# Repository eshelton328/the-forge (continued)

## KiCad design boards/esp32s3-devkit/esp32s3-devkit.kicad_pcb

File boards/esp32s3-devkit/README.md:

# ESP32-S3 DevKit

Development board built around the [ESP32-S3-WROOM-1](https://www.espressif.com/sites/default/files/documentation/esp32-s3-wroom-1_wroom-1u_datasheet_en.pdf) module with an integrated [TPS63070](https://www.ti.com/lit/ds/symlink/tps63070.pdf) buck-boost converter and USB-C connectivity.

## Specifications

- **MCU**: ESP32-S3-WROOM-1 (Wi-Fi + BLE, dual-core, 32-bit)
- **Power**: battery only — 3×AA (≈3.0–4.8 V) on the VBAT header pin, through reverse-polarity PFET (Q1) and power switch (SW1) into a TPS63070 buck-boost (3.3 V regulated output)
- **Interface**: USB-C (USB 2.0, 16-pin receptacle) — **data only, by design**; VBUS does not power the board. Batteries must be connected and SW1 on to flash.
- **ESD protection**: USBLC6-2SC6 on USB data lines
- **Layers**: 4
- **Thickness**: 1.6mm
- **Fab targets**: JLCPCB 4-layer advanced
- **Input voltage note**: the TPS63070 accepts up to 16 V, but C3 (10 µF 0402) is 6.3 V-rated — keep VBAT ≤ ~5.5 V unless C3 is upgraded (e.g. 0805/25 V)

## Key Components

| Ref | Value | Description |
|-----|-------|-------------|
| U1 | TPS63070RNMR | Buck-boost converter (3.3V output, adjustable) |
| U2 | ESP32-S3-WROOM-1 | Wi-Fi + BLE SoC module |
| U3 | USBLC6-2SC6 | USB ESD protection |
| J1, J2 | Conn_01x17 | GPIO breakout headers (J1 pin 2 = VBAT battery input) |
| J3 | USB-C 16P | USB-C receptacle (USB 2.0, data only) |
| L1 | 1.5µH | Buck-boost inductor (XFL4020-152ME) |
| Q1 | AO3401A | Reverse-polarity protection PMOS (drain to battery) |
| SW1 | MK-12C03-G015 | SPDT slide switch — main power (latching ON/OFF) |
| SW2 | RESET | Push — ESP32 reset |
| SW3 | BOOT | Push — boot / download mode |
| D1, D3 | LED | Status indicators (D2 zener: DNP) |

## Flashing

First flash: batteries in, SW1 on, hold BOOT, tap RESET, release BOOT, then flash over native USB (CDC/DFU). Subsequent flashes work over USB without buttons.

<!-- board-images-start -->
## Board Images

_Auto-generated on merge to main._

### Schematic

### PCB Layout

| Top | Bottom |
| :---: | :---: |
|  |  |

<!-- board-images-end -->

<!-- drc-summary-start -->
## KiCad design checks

_Same layout as the KiCad check summary on pull requests (ERC, DRC, fab rules). Auto-generated on merge to main._

| Check | Result |
|:------|:-------|
| ERC | ✅ |
| DRC | 🔴 12 errors |
| Fab: jlcpcb-4layer-advanced | ✅ |

<details>
<summary><strong>DRC</strong> — 🔴 12 errors</summary>

> **Violations** (12)
>
> <details>
> <summary>🔴 <b><code>clearance</code></b> — 8 errors</summary>
>
> Clearance violation (zone clearance 0.2000 mm; actual 0.1217 mm)
> - `Track [Net-(Q1-G)] on F.Cu, length 0.4725 mm` / `Zone [/PFET] on F.Cu, priority 2`
> - `Via [Net-(Q1-G)] on F.Cu - B.Cu` / `Zone [GND] on B.Cu, priority 0`
> - `Via [Net-(Q1-G)] on F.Cu - B.Cu` / `Zone [GND] on In1.Cu, priority 0`
> - `Via [Net-(Q1-G)] on F.Cu - B.Cu` / `Zone [GND] on B.Cu, priority 0`
> - `Via [Net-(Q1-G)] on F.Cu - B.Cu` / `Zone [GND] on In1.Cu, priority 0`
> - `Track [Net-(Q1-G)] on B.Cu, length 1.1500 mm` / `Zone [GND] on B.Cu, priority 0`
> - `Track [Net-(Q1-G)] on B.Cu, length 2.5000 mm` / `Zone [GND] on B.Cu, priority 0`
> - `Pad 1 [Net-(Q1-G)] of Q1 on F.Cu` / `Zone [/PFET] on F.Cu, priority 2`
>
> </details>
>
> <details>
> <summary>🔴 <b><code>hole_clearance</code></b> — 4 errors</summary>
>
> Hole clearance violation (board setup constraints hole clearance 0.2500 mm; actual 0.0000 mm)
> - `Via [Net-(Q1-G)] on F.Cu - B.Cu` / `Zone [GND] on B.Cu, priority 0`
> - `Via [Net-(Q1-G)] on F.Cu - B.Cu` / `Zone [GND] on In1.Cu, priority 0`
> - `Via [Net-(Q1-G)] on F.Cu - B.Cu` / `Zone [GND] on B.Cu, priority 0`
> - `Via [Net-(Q1-G)] on F.Cu - B.Cu` / `Zone [GND] on In1.Cu, priority 0`
>
> </details>
>
</details>

<!-- drc-summary-end -->

## Status

**In Development** — schematic and initial PCB layout complete. Not yet fabricated.

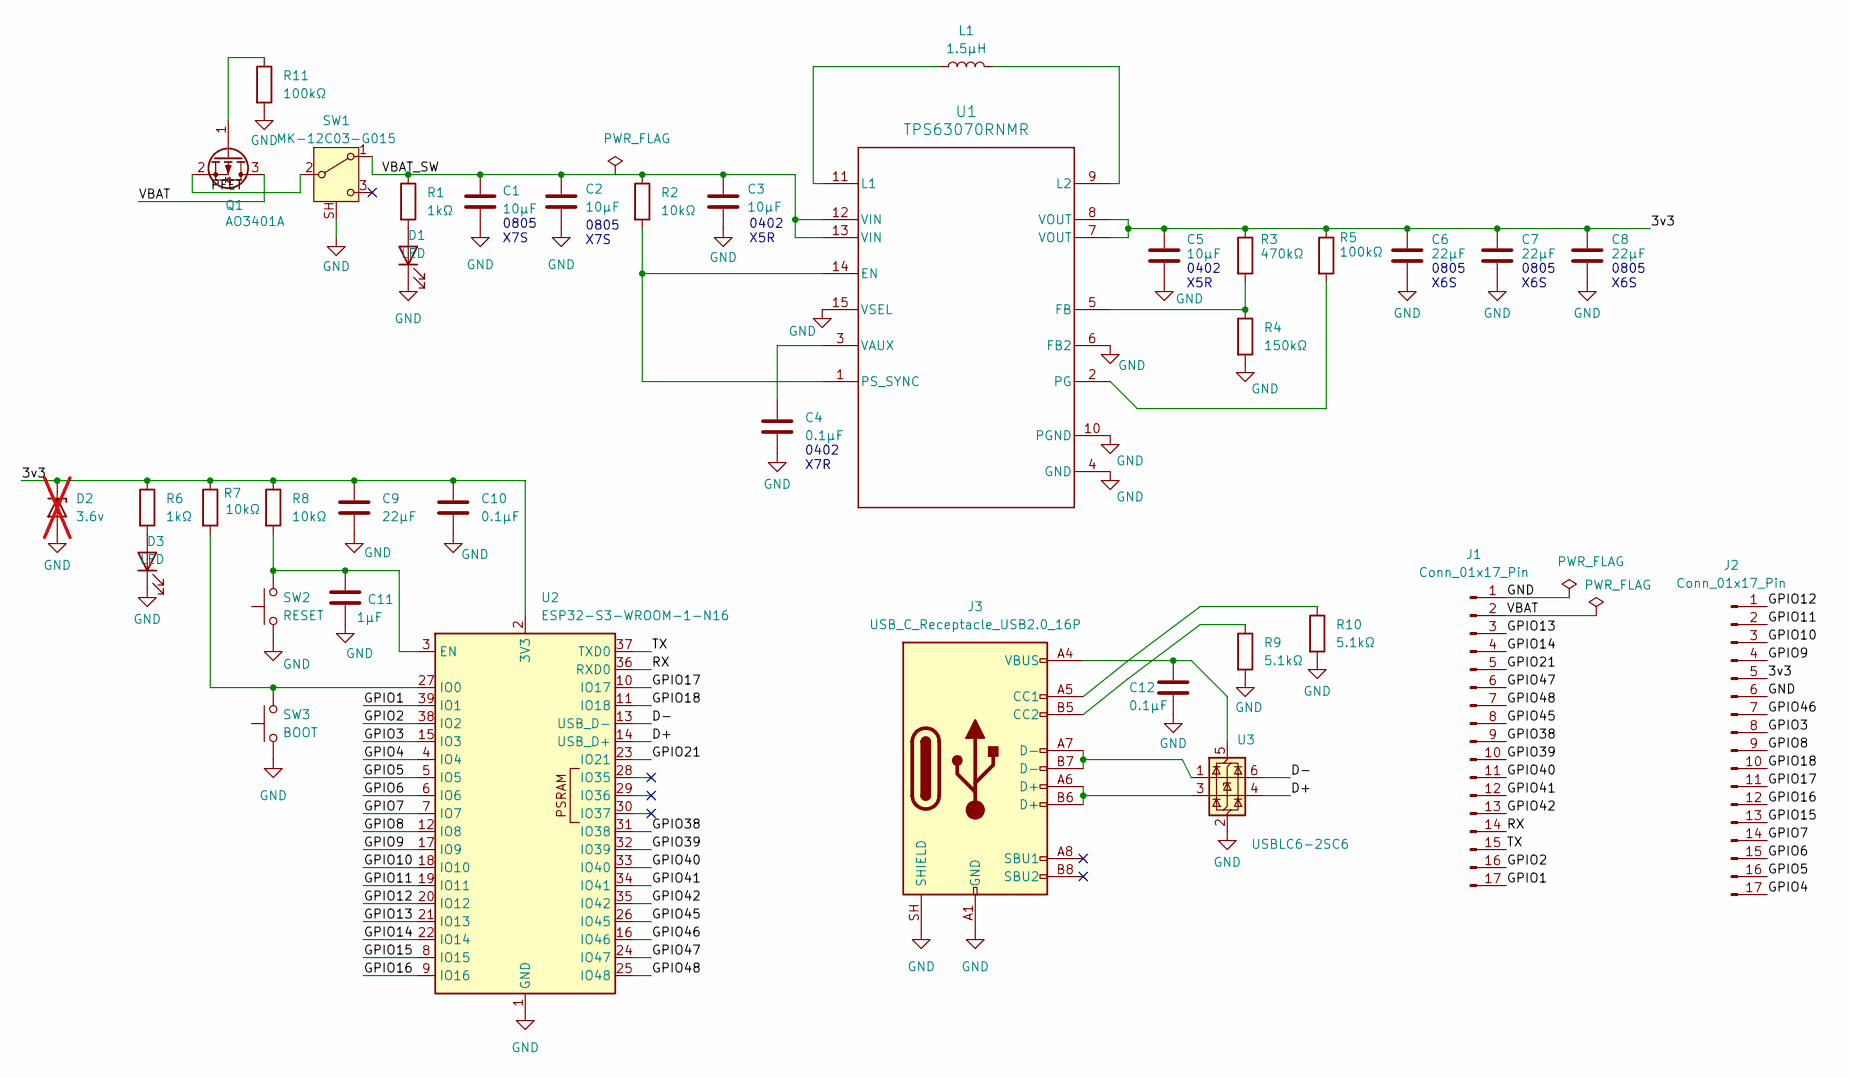
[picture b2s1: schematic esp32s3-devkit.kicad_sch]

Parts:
C1, C2: 10µF; C_0805_2012Metric
C3, C5: 10µF; C_0402_1005Metric
C4, C10, C12: 0.1µF; C_0402_1005Metric
C6, C7, C8, C9: 22µF; C_0805_2012Metric
C11: 1µF; C_0402_1005Metric
D1, D3: LED; LED_0603_1608Metric
D2: 3.6v; D_SOD-323; not fitted
J1, J2: Conn_01x17_Pin; PinHeader_1x17_P2.54mm_Vertical
J3: USB_C_Receptacle_USB2.0_16P; USB_C_Receptacle_HRO_TYPE-C-31-M-12
L1: 1.5µH; IND_XFL4020-152MEC
Q1: AO3401A; SOT-23
R1, R6: 1kΩ; R_0402_1005Metric
R2, R7, R8: 10kΩ; R_0402_1005Metric
R3: 470kΩ; R_0402_1005Metric
R4: 150kΩ; R_0402_1005Metric
R5, R11: 100kΩ; R_0402_1005Metric
R9, R10: 5.1kΩ; R_0402_1005Metric
SW1: MK-12C03-G015; SW_SPDT_Shouhan_MSK12C02
SW2: RESET; SW_Push_1P1T_XKB_TS-1187A
SW3: BOOT; SW_Push_1P1T_XKB_TS-1187A
U1: TPS63070RNMR; TPS63070
U2: ESP32-S3-WROOM-1-N16; ESP32-S3-WROOM-1
U3: USBLC6-2SC6; SOT-23-6

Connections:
/3v3: C5.1, C6.1, C7.1, C8.1, C9.1, C10.1, D2.1 (K), J2.5, R3.1, R5.1, R6.1, R7.1, R8.1, U1.7 (VOUT), U1.8 (VOUT), U2.2 (3V3)
/D+: U2.14 (USB_D+), U3.4 (I/O2)
/D-: U2.13 (USB_D-), U3.6 (I/O1)
/GPIO1: J1.17, U2.39 (IO1)
/GPIO2: J1.16, U2.38 (IO2)
/GPIO3: J2.8, U2.15 (IO3)
/GPIO4: J2.17, U2.4 (IO4)
/GPIO5: J2.16, U2.5 (IO5)
/GPIO6: J2.15, U2.6 (IO6)
/GPIO7: J2.14, U2.7 (IO7)
/GPIO8: J2.9, U2.12 (IO8)
/GPIO9: J2.4, U2.17 (IO9)
/GPIO10: J2.3, U2.18 (IO10)
/GPIO11: J2.2, U2.19 (IO11)
/GPIO12: J2.1, U2.20 (IO12)
/GPIO13: J1.3, U2.21 (IO13)
/GPIO14: J1.4, U2.22 (IO14)
/GPIO15: J2.13, U2.8 (IO15)
/GPIO16: J2.12, U2.9 (IO16)
/GPIO17: J2.11, U2.10 (IO17)
/GPIO18: J2.10, U2.11 (IO18)
/GPIO21: J1.5, U2.23 (IO21)
/GPIO38: J1.9, U2.31 (IO38)
/GPIO39: J1.10, U2.32 (IO39)
/GPIO40: J1.11, U2.33 (IO40)
/GPIO41: J1.12, U2.34 (IO41)
/GPIO42: J1.13, U2.35 (IO42)
/GPIO45: J1.8, U2.26 (IO45)
/GPIO46: J2.7, U2.16 (IO46)
/GPIO47: J1.6, U2.24 (IO47)
/GPIO48: J1.7, U2.25 (IO48)
/PFET: Q1.2 (S), SW1.2 (B)
/RX: J1.14, U2.36 (RXD0)
/TX: J1.15, U2.37 (TXD0)
/VBAT: J1.2, Q1.3 (D)
/VBAT_SW: C1.1, C2.1, C3.1, R1.1, R2.1, SW1.1 (A), U1.12 (VIN), U1.13 (VIN)
GND: C1.2, C2.2, C3.2, C4.2, C5.2, C6.2, C7.2, C8.2, C9.2, C10.2, C11.2, C12.2, D1.1 (K), D2.2 (A), D3.1 (K), J1.1, J2.6, J3.A1 (GND), J3.A12 (GND), J3.B1 (GND), J3.B12 (GND), J3.SH (SHIELD), R4.2, R9.2, R10.2, R11.2, SW1.SH (SHIELD), SW2.1, SW3.1, U1.4 (GND), U1.6 (FB2), U1.10 (PGND), U1.15 (VSEL), U2.1 (GND), U2.40 (GND), U2.41 (GND), U3.2 (GND)
unnamed: D1.2 (A), R1.2
unnamed: D3.2 (A), R6.2
unnamed: J3.A5 (CC1), R10.1
unnamed: J3.B5 (CC2), R9.1
unnamed: J3.A6 (D+), J3.B6 (D+), U3.3 (I/O2)
unnamed: J3.A7 (D-), J3.B7 (D-), U3.1 (I/O1)
unnamed: Q1.1 (G), R11.1
unnamed: R2.2, U1.1 (PS_SYNC), U1.14 (EN)
unnamed: R3.2, R4.1, U1.5 (FB)
unnamed: L1.1, U1.11 (L1)
unnamed: L1.2, U1.9 (L2)
unnamed: R5.2, U1.2 (PG)
unnamed: C4.1, U1.3 (VAUX)
unnamed: C11.1, R8.2, SW2.2, U2.3 (EN)
unnamed: R7.2, SW3.2, U2.27 (IO0)
unnamed: C12.1, J3.A4 (VBUS), J3.A9 (VBUS), J3.B4 (VBUS), J3.B9 (VBUS), U3.5 (VBUS)

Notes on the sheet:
0805 X7S
0805 X6S
0402 X7R
0402 X5R

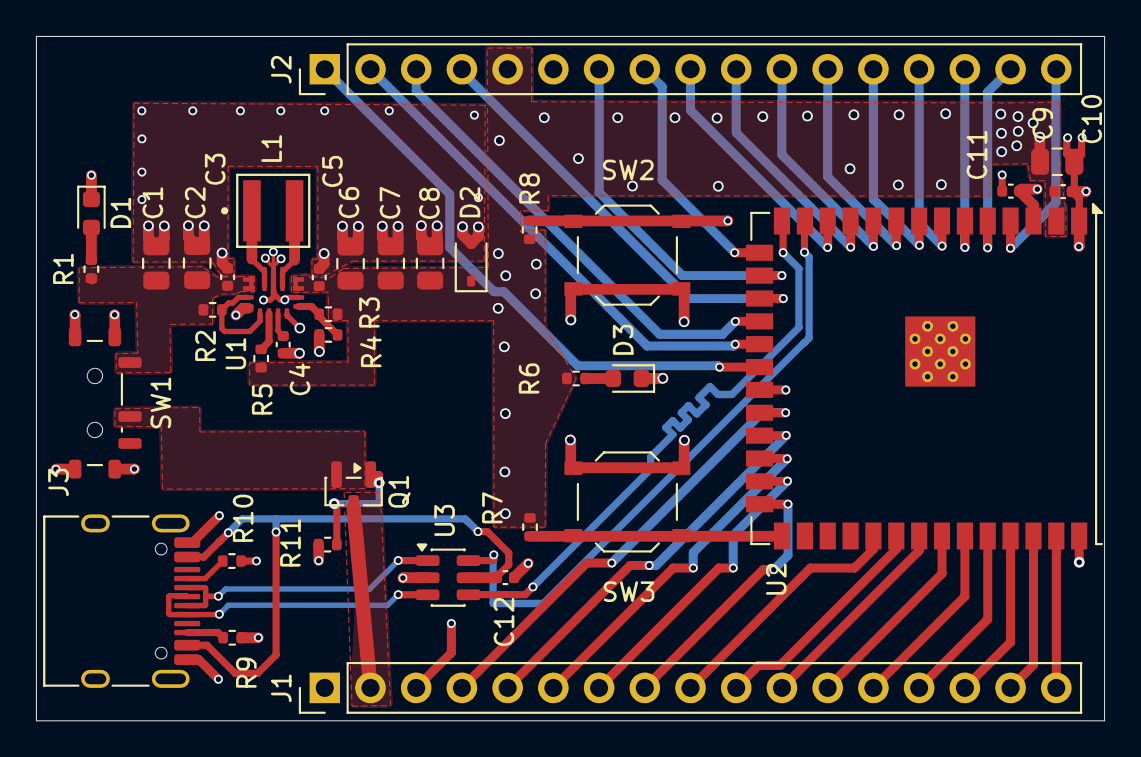
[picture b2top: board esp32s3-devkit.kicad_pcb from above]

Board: 4 copper layers, 59.3 x 38.0 mm, 37 parts (0 on the bottom side), 53 nets.

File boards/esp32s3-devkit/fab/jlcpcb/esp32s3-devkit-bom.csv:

Comment,Designator,Footprint,LCSC
10uF,C1 C2,C_0805_2012Metric,C15850
10uF,C3 C5,C_0402_1005Metric,C15525
0.1uF,C4 C10 C11 C12,C_0402_1005Metric,C1525
22uF,C6 C7 C8 C9,C_0805_2012Metric,C45783
LED,D1 D3,LED_0603_1608Metric,C2286
USB_C_Receptacle_USB2.0_16P,J3,USB_C_Receptacle_HRO_TYPE-C-31-M-12,C165948
1.5uH,L1,IND_XFL4020-152MEC,C3033018
AO3401A,Q1,SOT-23,C15127
1k,R1 R6,R_0402_1005Metric,C11702
10k,R2 R7 R8,R_0402_1005Metric,C60490
470k,R3,R_0402_1005Metric,C156107
150k,R4,R_0402_1005Metric,C25755
100k,R5 R11,R_0402_1005Metric,C25741
5.1k,R9 R10,R_0402_1005Metric,C25905
MK-12C03-G015,SW1,SW_SPDT_Shouhan_MSK12C02,C2890358
RESET,SW2,SW_Push_1P1T_XKB_TS-1187A,C318884
BOOT,SW3,SW_Push_1P1T_XKB_TS-1187A,C318884
TPS63070RNMR,U1,TPS63070,C109322
ESP32-S3-WROOM-1-N16,U2,ESP32-S3-WROOM-1,C2913199
USBLC6-2SC6,U3,SOT-23-6,C7519

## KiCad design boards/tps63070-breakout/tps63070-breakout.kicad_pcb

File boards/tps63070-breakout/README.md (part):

# TPS63070 Buck-Boost Breakout

Standalone breakout board for the [TPS63070](https://www.ti.com/lit/ds/symlink/tps63070.pdf) buck-boost converter. Provides a regulated 3.3V output from a wide input voltage range (2V–16V).

## Specifications

- **Input voltage**: 2V – 16V
- **Output voltage**: 3.3V (default, configurable via feedback divider)
- **Output current**: up to 2A
- **Layers**: 2
- **Thickness**: 1.6mm
- **Fab targets:** JLCPCB / PCBWay **2-layer advanced** (see [`board.yml`](board.yml)); CI matches `make fab-drc` for this board using those decks.

## Bill of Materials

| Ref | Value | Part Number | Datasheet |
|-----|-------|-------------|-----------|
| U1 | TPS63070 | TPS630701RNMR | [TI TPS63070](https://www.ti.com/lit/ds/symlink/tps63070.pdf) |
| L1 | 1.5µH | XFL4020-152MEC | [Coilcraft XFL4020](https://www.coilcraft.com/en-us/products/power/shielded-inductors/molded-inductors/xfl/xfl4020/) |
| C1, C2, C3 | 10µF | — | Input decoupling |
| C4 | 0.1µF | — | VAUX decoupling |
| C5 | 10µF | — | Output decoupling |
| C6, C7, C8 | 22µF | — | Output bulk capacitance |
| R1 | 10kΩ | — | EN pull-up |
| R2 | 470kΩ | — | Feedback divider (upper) |
| R3 | 150kΩ | — | Feedback divider (lower) |
| R4 | 100kΩ | — | FB → FB2 scaling resistor |
| J1 | 4-pin header | — | VIN, GND, VOUT, PG |

## Output Voltage Variants

The output voltage is set by the feedback resistor divider (R2/R3): `V_OUT = V_REF × (1 + R2 / R3)` where V_REF = 0.8V. See the [TPS63070 datasheet](https://www.ti.com/lit/ds/symlink/tps63070.pdf) §9.2.2.1 for the formula and recommended values.

| Output Voltage | R2 (upper) | R3 (lower) | Status |
|---------------|-----|-----|--------|
| 3.3V | 470kΩ | 150kΩ | Default configuration |
| 5V | — | — | Planned ([#4](https://github.com/eshelton328/the-forge/issues/4)) |

<!-- board-images-start -->
## Board Images

_Auto-generated on merge to main._

### Schematic

### PCB Layout

| Top | Bottom |
| :---: | :---: |
|  |  |

<!-- board-images-end -->

<!-- drc-summary-start -->
## KiCad design checks

_Same layout as the KiCad check summary on pull requests (ERC, DRC, fab rules). Auto-generated on merge to main._

| Check | Result |
|:------|:-------|
| ERC | ✅ |
| DRC | ✅ |
| Fab: jlcpcb-2layer-advanced | ✅ |
| Fab: pcbway-2layer-advanced | ✅ |

<!-- drc-summary-end -->

<!-- validation-summary-start -->
## Validation Summary

_Run `make validate tps63070-breakout` to regenerate locally._

| Check | Status | Details |
|-------|--------|---------|
| required_components | pass | 15/15 components present |
| required_nets | pass | 3/3 nets present |
| capacitor_budget | pass | input: 30µF (min 20µF); output: 76µF (min 60µF); decoupling: C4 |
| voltage_divider | pass | V_OUT = 3.307V (target 3.3V, 0.20% error) — R2=470kΩ, R3=150kΩ, V_REF=0.8V |
| bom_rules | pass | footprints required; no duplicate refs; datasheets on U1 |
<!-- validation-summary-end -->

## Simulation (ngspice)

CI uploads **`docs/spice-report.md`**, **`docs/spice-report.metrics.json`**, and netlists under artifact **`spice-boards`** → `tps63070-breakout/`. Example folder layout: [`docs/spice-report-example.md`](docs/spice-report-example.md).

| Read this | Open this |
| :--- | :--- |
| Scenario limits (voltages, ripple, AC anchors) | [`sim.yml`](sim.yml) |
| Assembled overlay wrapper (`extracted` + `manual` + transient bundle) | [`sim/overlay.cir`](sim/overlay.cir) |
| Extended transient stimulus timeline (`PWL`, pulse bursts, low-VIN heavy-load segment) | [`sim/transient_stress_body.cir`](sim/transient_stress_body.cir) |
| Primary `.meas` bundle (legacy windows + extended stress probes) | [`sim/overlay_measures.cir`](sim/overlay_measures.cir) |
| Line-transfer small-signal `.ac` (VIN AC → Vout tap) | [`sim/ac_small_signal.cir`](sim/ac_small_signal.cir) |
| Norton output impedance probes (`ac_z_out`) | [`sim/ac_z_out.cir`](sim/ac_z_out.cir) |
| Norton input impedance probes (`ac_z_in`; bench `RBENCH` — see deck comments) | [`sim/ac_z_in.cir`](sim/ac_z_in.cir) |
| Startup ramp proxy (VIN slew into light load) | [`sim/tran_startup_ramp.cir`](sim/tran_startup_ramp.cir) |
| Lump-cap stub corner (+470 p at far load node; compares ripple anchors) | [`sim/tran_corner_stub_cap.cir`](sim/tran_corner_stub_cap.cir), [`sim/corner_load_470p.cir`](sim/corner_load_470p.cir) |
| Layout-ish parasitics (distribution, stubs) | [`sim/extracted_hotloop_fragment.cir`](sim/extracted_hotloop_fragment.cir), [`sim/manual_parasitics.cir`](sim/manual_parasitics.cir) |
| Parasitic workflow / reviewer expectations | [`sim/OVERLAY-PARASITICS.md`](../../sim/OVERLAY-PARASITICS.md) |
| Full runner / Docker / local commands | [`sim/README.md`](../../sim/README.md) |

**Flow:** KiCad exports **`sim/kicad_export.cir`** (gitignored); assembly merges vendor **`libs/spice`** → export → **`overlay.cir`**. The TI model in-repo is an **ngspice behavioral stub** — see [`libs/spice/README.md`](../../libs/spice/README.md) for what that implies.

Context: [#76](https://github.com/eshelton328/the-forge/issues/76) (transient regression), [#79](https://github.com/eshelton328/the-forge/issues/79) (multi-pass `.ac`), [#74](https://github.com/eshelton328/the-forge/issues/74) (overlay fragments).

### Simulation roadmap (long-term)

Goals for automated **design evidence** beyond today’s transient limits (not necessarily all in ngspice alone):

1. **Expected voltage output** — richer reporting vs nominal/datasheet-style bands (line/load tables, ripple budgets, multi-point summaries in artifacts).
2. **Impedance** — frequency-domain or port metrics (e.g. output impedance, PDN **|Z(f)|**) using `.ac` / richer models and, where needed, layout-linked overlays ([`sim/OVERLAY-PARASITICS.md`](../../sim/OVERLAY-PARASITICS.md), [#74](https://github.com/eshelton328/the-forge/issues/74)).
3. **EMI-oriented reporting** — structured EMI-adjacent summaries where the toolchain supports them (e.g. harmonic estimates, documented coupling assumptions); **not** chamber certification or guaranteed emissions compliance ([PRD #43](https://github.com/eshelton328/the-forge/issues/43) scope boundaries).

**Today:** transient + load-step regression ([#76](https://github.com/eshelton328/the-forge/issues/76)); **extended rail** (duty-cycled load bursts, low-VIN + heavy load, overshoot probes); **startup ramp** + **stub-cap corner** secondaries; AC **line-response** + Norton **|Zout| / |Zin|** (`ac_small_signal.cir`, `ac_z_out.cir`, `ac_z_in.cir`; [#79](https://github.com/eshelton328/the-forge/issues/79)).

**Repo tracking (scope / prioritization):** EMI-adjacent documentation expectations — [#81](https://github.com/eshelton328/the-forge/issues/81); scheduling non-sim backlog (PRD remainder, hardware variants such as [#4](https://github.com/eshelton328/the-forge/issues/4)) — [#82](https://github.com/eshelton328/the-forge/issues/82).

<!-- spice-regression-start -->
## SPICE regression (ngspice)

_Auto-generated when `docs/spice-report.metrics.json` is present (see `sim.yml` and [`sim/README.md`](../../sim/README.md))._

**Last metrics refresh:** 2026-07-06T21:07:49Z · **Overall:** PASS (schema v2)

[Full report (`docs/spice-report.md`)](docs/spice-report.md)

| Scenario | Measure | Value | Bounds | Result |
|:---------|:--------|:------|:-------|:-------|
| vin_bias_op | VIN rail DC (after input distribution) | 10 | min 9.99, max 10.01 | **PASS** |
| tran_settle | Vout steady (post transient) | 3.30704 | min 3.28, max 3.32 | **PASS** |
| tran_settle | Vout minimum over transient | 3.30704 | min 3.25 | **PASS** |
| tran_settle | Output ripple peak-peak | 0 | max 0.15 | **PASS** |
| tran_load_step | Vout at light load sample | 3.30704 | min 3.25, max 3.35 | **PASS** |
| tran_load_step | Vout at heavy load sample | 3.30704 | min 3.28, max 3.32 | **PASS** |
| tran_load_step | Vout peak during first heavy-load step (118–135 µs) | 3.30704 | max 3.45 | **PASS** |
| tran_load_step | Vout sample after heavy-load step (160 µs) | 3.30704 | min 3.25, max 3.34 | **PASS** |
| tran_stress_extended | Vout minimum during duty-cycled load bursts (276–318 µs) | 3.30704 | min 3.15 | **PASS** |
| tran_stress_extended | Vout peak-peak during load bursts (276–318 µs) | 0 | max 0.35 | **PASS** |
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
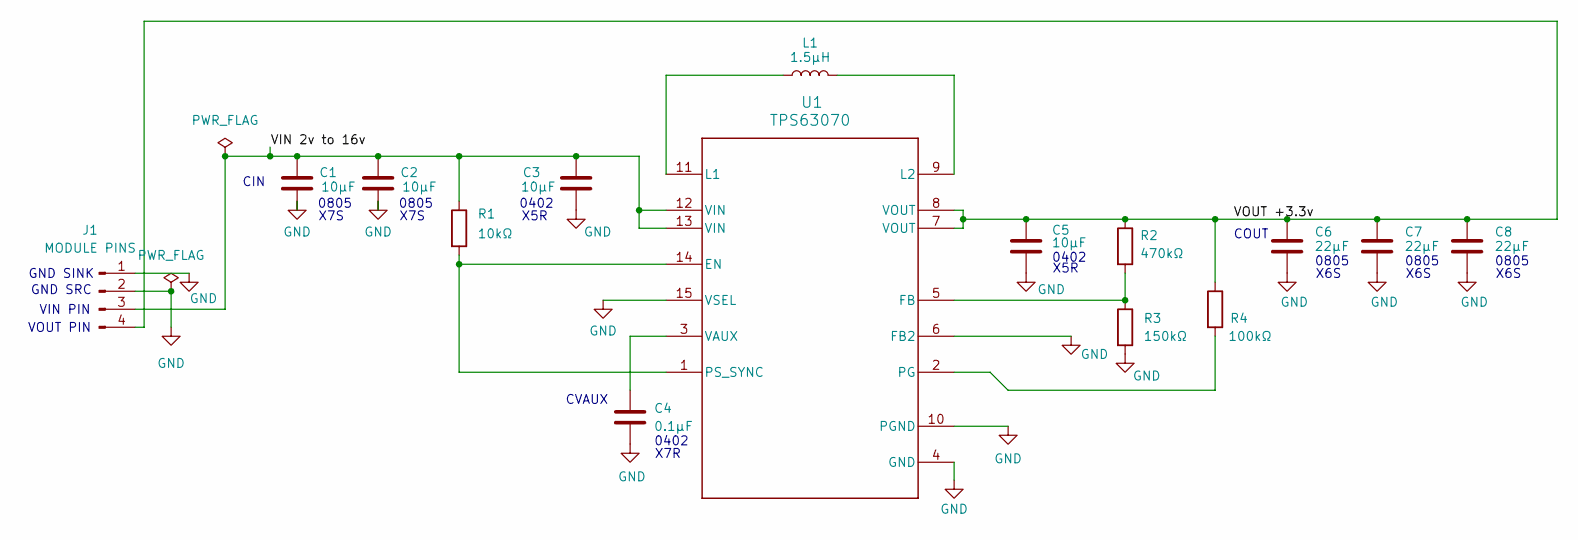
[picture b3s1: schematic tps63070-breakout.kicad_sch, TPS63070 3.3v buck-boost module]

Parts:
C1, C2: 10µF; C_0805_2012Metric
C3, C5: 10µF; C_0402_1005Metric
C4: 0.1µF; C_0402_1005Metric
C6, C7, C8: 22µF; C_0805_2012Metric
J1: MODULE PINS; PinHeader_1x04_P2.54mm_Vertical
L1: 1.5µH; IND_XFL4020-152MEC
R1: 10kΩ; R_0402_1005Metric
R2: 470kΩ; R_0402_1005Metric
R3: 150kΩ; R_0402_1005Metric
R4: 100kΩ; R_0402_1005Metric
U1: TPS63070

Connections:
/VIN 2v to 16v: C1.1, C2.1, C3.1, J1.3, R1.1, U1.12 (VIN), U1.13 (VIN)
/VOUT +3.3v: C5.1, C6.1, C7.1, C8.1, J1.4, R2.1, R4.1, U1.7 (VOUT), U1.8 (VOUT)
GND: C1.2, C2.2, C3.2, C4.2, C5.2, C6.2, C7.2, C8.2, J1.1, J1.2, R3.2, U1.4 (GND), U1.6 (FB2), U1.10 (PGND), U1.15 (VSEL)
unnamed: R1.2, U1.1 (PS_SYNC), U1.14 (EN)
unnamed: R2.2, R3.1, U1.5 (FB)
unnamed: L1.1, U1.11 (L1)
unnamed: L1.2, U1.9 (L2)
unnamed: R4.2, U1.2 (PG)
unnamed: C4.1, U1.3 (VAUX)

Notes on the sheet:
0805
X6S
0402
X7S
VOUT PIN
GND SRC
CVAUX
X5R
CIN
GND SINK
COUT
X7R
VIN PIN

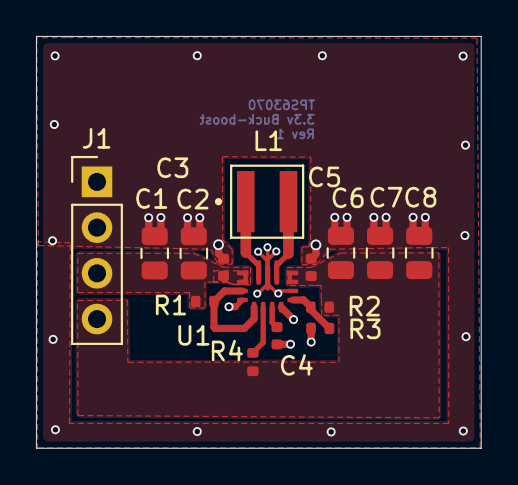
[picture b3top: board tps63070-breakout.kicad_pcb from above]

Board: 2 copper layers, 24.7 x 22.9 mm, 15 parts (0 on the bottom side), 9 nets.

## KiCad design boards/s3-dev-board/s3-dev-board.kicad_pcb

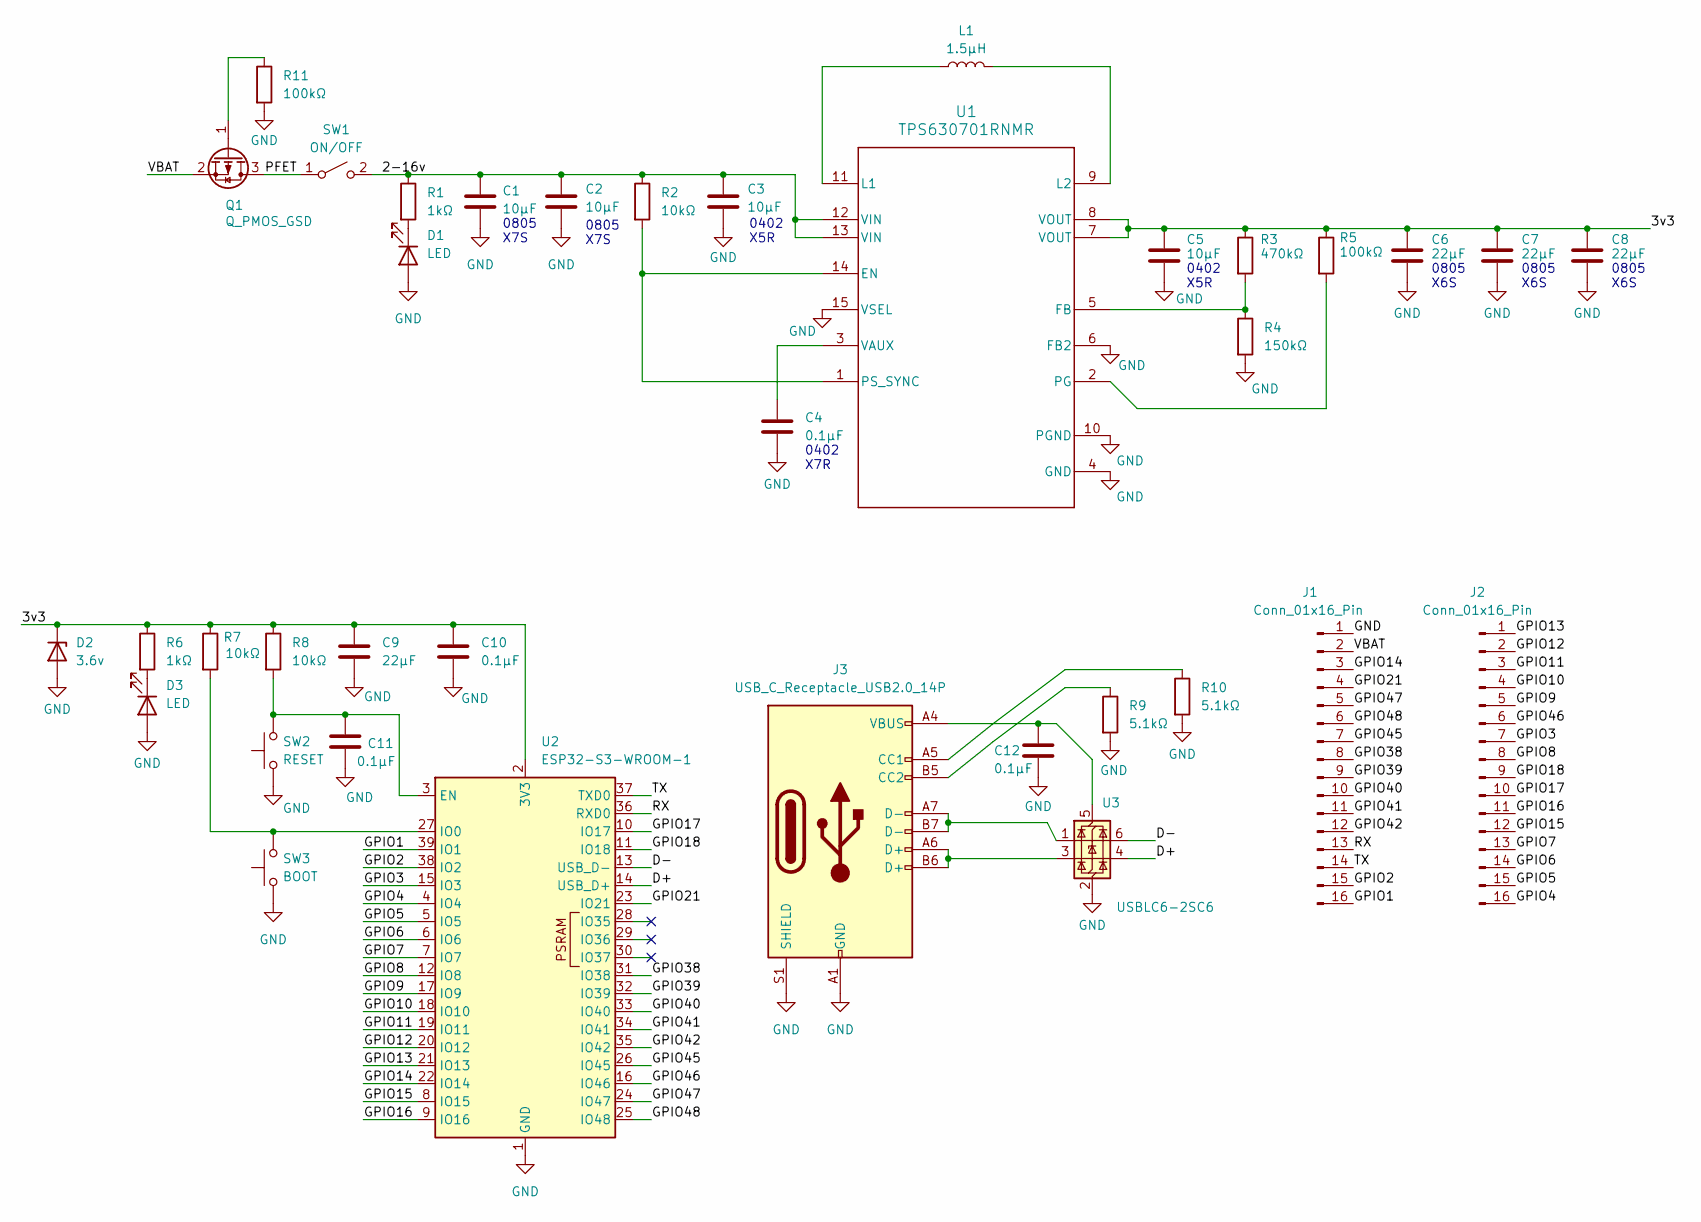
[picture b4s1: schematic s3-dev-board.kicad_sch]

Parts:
C1, C2: 10µF; C_0805_2012Metric
C3, C5: 10µF; C_0402_1005Metric
C4, C10, C11, C12: 0.1µF; C_0402_1005Metric
C6, C7, C8, C9: 22µF; C_0805_2012Metric
D1, D3: LED; LED_0603_1608Metric
D2: 3.6v; D_SOD-323
J1, J2: Conn_01x16_Pin; PinHeader_1x16_P2.54mm_Vertical
J3: USB_C_Receptacle_USB2.0_14P; USB_C_Receptacle_HRO_TYPE-C-31-M-12
L1: 1.5µH; IND_XFL4020-152MEC
Q1: Q_PMOS_GSD; SOT-23
R1, R6: 1kΩ; R_0402_1005Metric
R2, R7, R8: 10kΩ; R_0402_1005Metric
R3: 470kΩ; R_0402_1005Metric
R4: 150kΩ; R_0402_1005Metric
R5, R11: 100kΩ; R_0402_1005Metric
R9, R10: 5.1kΩ; R_0402_1005Metric
SW1: ON/OFF; SW_SPST_CK_RS282G05A3
SW2: RESET; SW_SPST_TL3342
SW3: BOOT; SW_SPST_TL3342
U1: TPS630701RNMR; TPS63070
U2: ESP32-S3-WROOM-1
U3: USBLC6-2SC6; SOT-23-6

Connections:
/2-16v: C1.1, C2.1, C3.1, R1.1, R2.1, SW1.2 (B), U1.12 (VIN), U1.13 (VIN)
/3v3: C5.1, C6.1, C7.1, C8.1, C9.1, C10.1, D2.1 (K), R3.1, R5.1, R6.1, R7.1, R8.1, U1.7 (VOUT), U1.8 (VOUT), U2.2 (3V3)
/D+: U2.14 (USB_D+), U3.4 (I/O2)
/D-: U2.13 (USB_D-), U3.6 (I/O1)
/GPIO1: J1.16, U2.39 (IO1)
/GPIO2: J1.15, U2.38 (IO2)
/GPIO3: J2.7, U2.15 (IO3)
/GPIO4: J2.16, U2.4 (IO4)
/GPIO5: J2.15, U2.5 (IO5)
/GPIO6: J2.14, U2.6 (IO6)
/GPIO7: J2.13, U2.7 (IO7)
/GPIO8: J2.8, U2.12 (IO8)
/GPIO9: J2.5, U2.17 (IO9)
/GPIO10: J2.4, U2.18 (IO10)
/GPIO11: J2.3, U2.19 (IO11)
/GPIO12: J2.2, U2.20 (IO12)
/GPIO13: J2.1, U2.21 (IO13)
/GPIO14: J1.3, U2.22 (IO14)
/GPIO15: J2.12, U2.8 (IO15)
/GPIO16: J2.11, U2.9 (IO16)
/GPIO17: J2.10, U2.10 (IO17)
/GPIO18: J2.9, U2.11 (IO18)
/GPIO21: J1.4, U2.23 (IO21)
/GPIO38: J1.8, U2.31 (IO38)
/GPIO39: J1.9, U2.32 (IO39)
/GPIO40: J1.10, U2.33 (IO40)
/GPIO41: J1.11, U2.34 (IO41)
/GPIO42: J1.12, U2.35 (IO42)
/GPIO45: J1.7, U2.26 (IO45)
/GPIO46: J2.6, U2.16 (IO46)
/GPIO47: J1.5, U2.24 (IO47)
/GPIO48: J1.6, U2.25 (IO48)
/PFET: Q1.3 (D), SW1.1 (A)
/RX: J1.13, U2.36 (RXD0)
/TX: J1.14, U2.37 (TXD0)
/VBAT: J1.2, Q1.2 (S)
GND: C1.2, C2.2, C3.2, C4.2, C5.2, C6.2, C7.2, C8.2, C9.2, C10.2, C11.2, C12.2, D1.2 (A), D2.2 (A), D3.2 (A), J1.1, J3.A1 (GND_A1), J3.A12 (GND_A12), J3.B1 (GND_B1), J3.B12 (GND_B12), J3.S1 (SHIELD), J3.SH (SHIELD_S1), R4.2, R9.2, R10.2, R11.2, SW2.1, SW3.1, U1.4 (GND), U1.6 (FB2), U1.10 (PGND), U1.15 (VSEL), U2.1 (GND), U2.40 (GND), U2.41 (GND), U3.2 (GND)
unnamed: D1.1 (K), R1.2
unnamed: D3.1 (K), R6.2
unnamed: J3.A5 (CC1_A5), R10.1
unnamed: J3.B5 (CC2_B5), R9.1
unnamed: J3.A6 (D+_A6), J3.B6 (D+_B6), U3.3 (I/O2)
unnamed: J3.A7 (D-_A7), J3.B7 (D-_B7), U3.1 (I/O1)
unnamed: Q1.1 (G), R11.1
unnamed: R2.2, U1.1 (PS_SYNC), U1.14 (EN)
unnamed: R3.2, R4.1, U1.5 (FB)
unnamed: L1.1, U1.11 (L1)
unnamed: L1.2, U1.9 (L2)
unnamed: R5.2, U1.2 (PG)
unnamed: C4.1, U1.3 (VAUX)
unnamed: C11.1, R8.2, SW2.2, U2.3 (EN)
unnamed: R7.2, SW3.2, U2.27 (IO0)
unnamed: C12.1, J3.A4 (VBUS_A4), J3.A9 (VBUS_A9), J3.B4 (VBUS_B4), J3.B9 (VBUS_B9), U3.5 (VBUS)

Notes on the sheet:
0805 X7S
0805 X6S
0402 X7R
0402 X5R

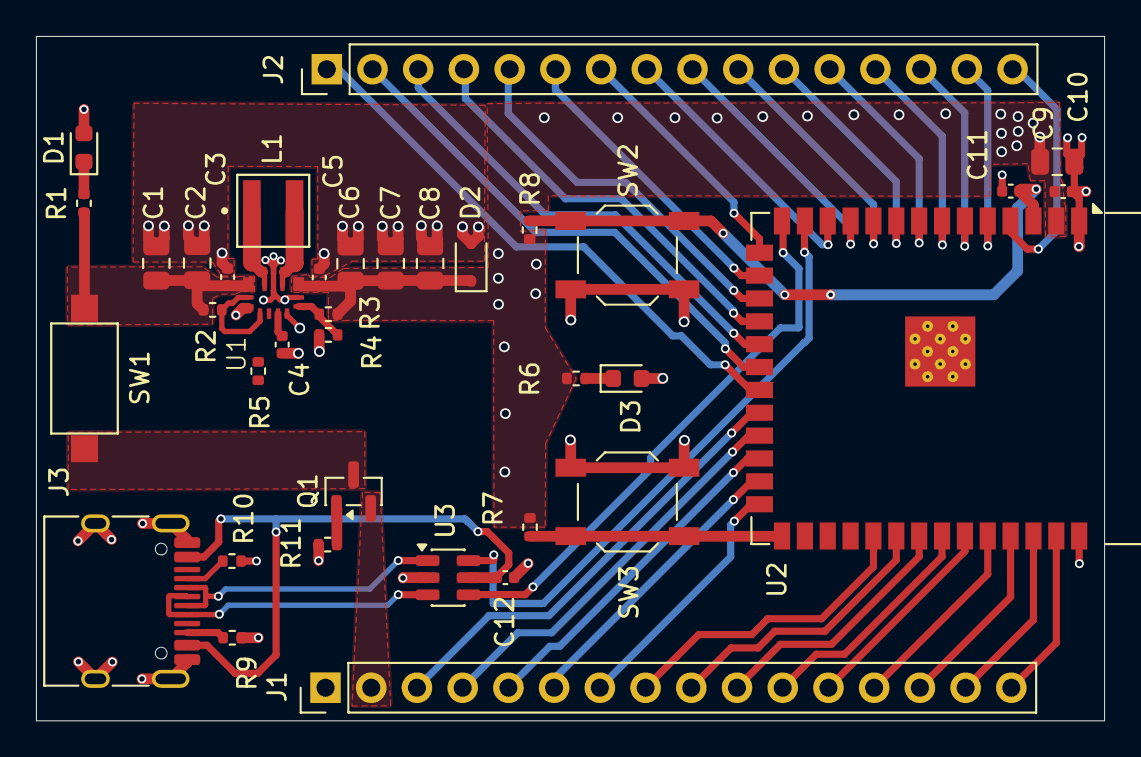
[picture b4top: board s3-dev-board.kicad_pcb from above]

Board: 4 copper layers, 59.3 x 38.0 mm, 37 parts (0 on the bottom side), 53 nets.

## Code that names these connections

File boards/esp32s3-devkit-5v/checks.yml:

# Board validation rules for esp32s3-devkit-5v (rev-2, dual rail)
# Used by scripts/validate_board.py to verify design intent beyond ERC/DRC.
#
# Power path: J1 VBAT -> Q1 reverse-protection PMOS -> PFET -> dual TPS63070.
# SW1 switches U1 EN only, via R31 10k; OFF throw and R32 pull EN to GND.
# Input chemistry/load remain provisional; cold start requires >=3V at VIN.
#   U1 -> 3.3V (SW1 enabled: ESP32, RTC, OLED switch, RGB LED, pull-ups)
#   U2 -> 5V   (GPIO18-gated via R19 pulldown: MAX98357A amp only)
# USB-C is data-only (VBUS biases ESD and the isolated presence detector); CC1 and CC2 each have 5.1k to GND.

required_components:
  Q4:
    value: "MMBT3904"
  Q5:
    value: "MMBT3904"
  Q6:
    value: "AO3401A"
  Q7:
    value: "MMBT3904"
  R40:
    value: "100k"
  R41:
    value: "1M"
  R42:
    value: "47k"
  R43:
    value: "10k"
  R44:
    value: "47k"
  R45:
    value: "100k"
  R46:
    value: "10k"
  R47:
    value: "100k"
  R48:
    value: "33k"
  R49:
    value: "10k"
  C34:
    value: "0.1uF"
  # --- regulators / power path ---
  U1:
    value: "TPS63070RNMR"
  U2:
    value: "TPS63070RNMR"
  Q1:
    value: "AO3401A"
  L1:
    value: "1.5µH"
  L2:
    value: "1.5µH"
  SW1:
    value: "MSK12C02"
  # --- MCU / interfaces ---
  U3:
    value: "ESP32-S3-WROOM-1-N16"
  U4:
    value: "USBLC6-2SC6"
  # --- rev-2 peripherals ---
  U5:
    value: "RV-3028-C7"     # RTC, I2C 0x52, /INT -> GPIO1 deep-sleep wake
  U6:
    value: "MAX98357A"      # I2S class-D amp on the 5V rail
  Q2:
    value: "AO3401A"        # OLED high-side load switch (GPIO41 via Q3)
  Q3:
    value: "MMBT3904"       # inverts GPIO41 so HIGH = OLED on
  D2:
    value: "150141M173100"       # status LED, common anode; active LOW, GPIO38/39/40
  # --- U1 3.3V stage ---
  R3:
    value: "10kΩ"           # U1 PS/SYNC pull-up to PFET: HIGH enables power save
  R4:
    value: "470kΩ"          # 3.3V FB divider upper
  R5:
    value: "150kΩ"          # 3.3V FB divider lower
  R6:
    value: "100kΩ"          # U1 PG pull-up
  C1:
    value: "10µF"           # U1 input caps (PFET)
  C2:
    value: "10µF"
  C3:
    value: "10µF"
  C4:
    value: "0.1µF"          # U1 VAUX cap — datasheet-required, must not be loaded
  # --- U2 5V stage ---
  R7:
    value: "10kΩ"           # U2 PS/SYNC pull-up to PFET: HIGH enables power save
  R8:
    value: "680kΩ"          # 5V FB divider upper
  R9:
    value: "130kΩ"          # 5V FB divider lower
  R10:
    value: "100kΩ"          # U2 PG pull-up
  R19:
    value: "100kΩ"          # U2 EN pulldown: 5V rail OFF until GPIO18 drives high
  C9:
    value: "10µF"           # U2 input caps (PFET)
  C10:
    value: "10µF"
  C11:
    value: "10µF"
  C12:
    value: "0.1µF"          # U2 VAUX cap
  # --- reverse protection / boot / USB ---
  R1:
    value: "100kΩ"          # Q1 gate pulldown
  R12:
    value: "10kΩ"           # IO0 (BOOT) pull-up
  R13:
    value: "10kΩ"           # EN pull-up
  C19:
    value: "1µF"            # EN reset RC
  R14:
    value: "5.1kΩ"          # USB-C CC pulldowns (sink identity)
  R15:
    value: "5.1kΩ"
  # --- I2C bus + RTC ---
  R16:
    value: "4.7kΩ"          # SCL pull-up on main RTC bus
  R17:
    value: "4.7kΩ"          # SDA pull-up
  R18:
    value: "10kΩ"           # RTC /INT pull-up (GPIO1)
  # --- amp control ---
  R20:
    value: "100kΩ"          # AMP_SD pulldown at U8 output; GPIO21 high = play
  # --- OLED load switch ---
  R21:
    value: "100kΩ"          # Q2 gate pull-up (default off)
  R22:
    value: "10kΩ"           # Q3 base resistor from GPIO41
  R23:
    value: "100kΩ"          # Q3 base pulldown (off at boot / deep sleep)
  # --- front panel ---
  R24:
    value: "10kΩ"           # button pull-ups (external: reliable EXT1 wake)
  R25:
    value: "10kΩ"
  R26:
    value: "10kΩ"
  R27:
    value: "10kΩ"
  C22:
    value: "0.1µF"          # button debounce
  C23:
    value: "0.1µF"
  C24:
    value: "0.1µF"
  C25:
    value: "0.1µF"
  R28:
    value: "330Ω"           # RGB red series
  R29:
    value: "150Ω"           # RGB green series
  R30:
    value: "150Ω"           # RGB blue series
  # --- misc ---
  R11:
    value: "1kΩ"            # D1 power LED series; DNP for low sleep current
  C21:
    value: "100µF"          # 3v3 bulk, drawn in the RTC block (1206)
  # --- amp-local caps (draw cluster at U6; place there in layout) ---
  C26:
    value: "100µF"          # amp burst reservoir
  C27:
    value: "10µF"           # amp mid-frequency
  C28:
    value: "0.1µF"          # amp HF decoupling at VDD pins 7/8
  J1: {}                    # battery JST-PH
  J2: {}                    # USB-C
  J3: {}                    # speaker JST-PH
  J4: {}                    # OLED header (switched VDD)
  SW2: {}                   # RESET
  SW3: {}                   # BOOT
  SW4:
    value: "VOL-"          # left button, GPIO4
  SW5:
    value: "MODE"          # center button, GPIO5
  SW6:
    value: "VOL+"          # right button, GPIO6
  SW7:
    value: "BATTERY"       # battery indication request, GPIO10, RTC-capable for wake

  # September 2026 power-state and USB corrections.
  U7:
    value: "SN74LVC2G66DCUR"
  U8:
    value: "SN74LVC1T45DBVR"
  R31:
    value: "10kΩ"
  R32:
    value: "100kΩ"
  R33:
    value: "10kΩ"
  R34:
    value: "22Ω"
  R35:
    value: "22Ω"
  R36:
    value: "100kΩ"
  R37:
    value: "4.7kΩ"
  R38:
    value: "4.7kΩ"
  R39:
    value: "100kΩ"
  C29:
    value: "0.1µF"
  C30:
    value: "0.1µF"
  C31:
    value: "1µF"
  C32:
    value: "0.1µF"
  C33:
    value: "0.1µF"

required_nets:
  - "GPIO2"
  - "GPIO7"
  - "GPIO12"
  - "GPIO13"
  - "GPIO15"
  - "GND"
  - "3v3"
  - "5v"
  - "VBAT"
  - "EN_3V3"
  - "USB_VBUS"
  - "USB_CC1"
  - "OLED_3V3"
  - "OLED_SCL"
  - "OLED_SDA"
  - "AMP_SD"
  - "GPIO11"
  - "RTC_VBACKUP"
  - "PFET"
  - "D+"
  - "D-"
  - "GPIO1"    # RTC /INT
  - "GPIO41"    # OLED power gate
  - "GPIO18"   # 5V boost enable
  - "GPIO21"   # amp SD_MODE

# These are nominal bookkeeping sums, not DC-bias-corrected capacitance or stability proof.
capacitor_budget:
  input_u1:
    min_total_uf: 20
    refs: [C1, C2, C3]
  input_u2:
    min_total_uf: 20
    refs: [C9, C10, C11]
  output_3v3:
    min_total_uf: 60
    refs: [C5, C6, C7, C8, C17, C21]
  output_5v:
    # U2 output caps (C13-C16, at the converter) + amp-local cluster
    # (C26 bulk reservoir, C27 mid, drawn at U6 for placement intent).
    # 186µF total — sized against the volume-induced brownouts this board
    # exists to fix.
    min_total_uf: 150
    refs: [C13, C14, C15, C16, C26, C27]
  decoupling:
    refs: [C4, C12, C18, C20, C28, C29, C30, C32, C33]

# TPS63070 feedback dividers: V_OUT = V_REF * (1 + R_upper / R_lower),
# V_REF = 0.8V per datasheet SLVSC58B §7.5. Guards the exact class of bug
# fixed in PR #107 (and now covers the new 5V rail too).
voltage_dividers:
  - name: "3.3V rail (U1)"
    v_ref: 0.8
    expected_voltage: 3.3
    tolerance_percent: 2.0
    upper_ref: R4
    lower_ref: R5
  - name: "5V rail (U2)"
    v_ref: 0.8
    expected_voltage: 5.0
    tolerance_percent: 2.0
    upper_ref: R8
    lower_ref: R9

bom_rules:
  require_footprint: true
  no_duplicate_refs: true
  require_datasheet_on: [U1, U2, U3, U4, U5, U6, U7, U8, Q1, Q2, Q3, Q4, Q5, Q6, Q7, L1, L2]

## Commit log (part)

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2026-04-25 Scaffold monorepo with s3-dev-board, multi-fab CI/CD, and shared libraries
    - Add s3-dev-board (ESP32-S3 + TPS63070 buck-boost + USB-C) under boards/
    - Set up shared libs/ for custom footprints (TPS63070.pretty), symbols, and 3D models
    - Create project-local fp-lib-table and sym-lib-table with portable KIPRJMOD paths
    - Add JLCPCB and PCBWay 4-layer DRC rule templates in fab-rules/
    - Add KiBot configs for JLCPCB, PCBWay, and documentation output generation
    - Add run-drc-all-fabs.sh script to test board against multiple fab houses
2026-04-26 Rename project branding: circuit-forge -> the-forge
    Made-with: Cursor
2026-04-26 fix(ci): avoid capturing test ls in all_boards output
    Redirect the glob existence check to /dev/null so CHANGED from all_boards only contains basenames, preventing duplicate matrix jobs (boards/foo/ vs foo).
    Made-with: Cursor
2026-04-26 fix(ci): install global KiCad lib tables in Docker before checks
    The kicad/kicad:10.0 image has no global sym-lib-table or fp-lib-table,
    so kicad-cli can't resolve standard libraries (Device, power, etc.).
    This inflated ERC from ~6 real issues to 104, and DRC similarly.
    Copy the bundled template lib tables into $HOME/.config/kicad/10.0/
    inside each container, using HOME=/workspace/.kicad-ci-home so the
    --user flag doesn't block writes to /home/kicad.
2026-04-26 fix(ci): deduplicate violation descriptions in PR comment
    Show the group description once, then list all affected items as
    flat bullets. Multi-item violations joined with / on one line.
    Made-with: Cursor
2026-04-26 fix(ci): add contents:read permission and simplify all_boards()
    Grant contents:read at workflow level so checkout works if the repo
    goes private; add it to the kicad-report job too (job-level perms
    replace the workflow default). Collapse the double-ls guard in
    all_boards() to a single pipeline.
    Made-with: Cursor
2026-04-26 fix(ci): cover SMD pad clearance and move base_ref to env block
    - JLCPCB pad/via rule now uses type-based condition instead of
    isPlated(), which excluded SMD pads (no hole = not plated).
    - Move github.base_ref interpolation from run: script into an env:
    mapping to match the injection-safe pattern used elsewhere.
    Made-with: Cursor
2026-04-26 fix: remove TODO.md and clean up script patterns
    Remove TODO.md — the GitHub Project board is the living task tracker.
    Aspirational items can be added to docs/ later if needed.
    Use mapfile for safer array sorting in the PR comment script.
    Made-with: Cursor
2026-04-26 fix: ignore footprint_symbol_field_mismatch in DRC parity check
    KiCad uses "" for empty fields in schematics and "~" in PCBs. The
    parity checker flags this as a mismatch on every component. Suppress
    this specific check in the project file rather than fighting KiCad
    on every save. Revert the schematic workaround so the file stays in
    its natural KiCad-saved state.
    Made-with: Cursor
2026-04-26 fix: set correct footprint library reference for TPS63070 symbol
    Change Footprint field from bare "RNM0015A" to "TPS63070:TPS63070"
    in the library symbol, embedded schematic copy, and U1 instance.
    Resolves the footprint_link_issues ERC warning — ERC now passes
    with 0 violations.
    Made-with: Cursor
2026-04-27 fix: resize vias on tps63070-breakout PCB for fab compliance
    Made-with: Cursor
2026-04-27 feat: add output voltage divider check for TPS63070
    Verifies the feedback resistor divider produces the expected output
    voltage using V_OUT = V_REF * (1 + R_upper / R_lower).
    For TPS63070: V_REF = 0.8V, R2 = 470kΩ, R3 = 150kΩ → 3.307V (±0.2%).
    Made-with: Cursor
2026-04-27 fix: replace raw SVG layer exports with 3D-rendered PCB layout images
    The kicad-cli pcb export svg command produces bare manufacturing-style
    output without board colors or styling. Switched PCB layout images to
    use the 3D renderer with orthographic projection and follow_pcb_editor
    preset, which shows proper solder mask, copper, and silkscreen colors.
    3D perspective renders now use --floor --perspective --rotate for an
    angled view with shadows.
2026-04-27 fix: detect new untracked images in update-readmes commit step
    git diff --quiet only sees changes to tracked files. The docs/ images
    are new untracked files on the first run, so the check passed and the
    commit was skipped. Stage files first with git add, then use
    git diff --cached --quiet to check the staging area instead.
    Made-with: Cursor
2026-04-27 ci: add board input to update-readmes workflow (#35)
    workflow_dispatch now accepts an optional board name to scope image
    generation and README updates to a single board. When blank, all
    boards are processed (same as the push trigger).
    Made-with: Cursor
2026-04-27 docs: fix esp32s3-devkit README — SW1 power, SW2 reset, SW3 boot
    Made-with: Cursor
2026-04-27 feat: README KiCad checks match PR format + fab DRC
    - update-board-readmes.py: ERC/DRC table and nested details like compose-kicad-report-comment.sh; fab drc-fab-*.json rows and details; optional board CLI arg\n- update-readmes.yml: run run-drc-all-fa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
    Made-with: Cursor
2026-04-27 chore(cursor): add Matt Pocock + caveman Cursor skills (#42)
    - grill-me, to-prd, to-issues, ubiquitous-language from mattpocock/skills
    - caveman from JuliusBrussee/caveman
    Each skill lives under .cursor/skills/<name>/SKILL.md beside pr-review.
    Made-with: Cursor
2026-04-28 feat(sim): board sim.yml assembly + overlay (#45) (#51)
    - Add assemble.py: fixed include order (includes → main → sim/overlay.cir)
    - Extend sim.yml with assembly block; mutual exclusion with netlist
    - discover_board_roots_with_sim_yml for opt-in boards
    - tps63070-breakout: sim.yml, sim/main.cir, sim/overlay.cir
    - Tests: assembler contract, discovery, config errors, ngspice integration
    - Makefile sim-board; gitignore assembled.cir and docs/spice-report.md
2026-04-29 ci(spice): PR workflow with path detection and artifacts
    - Add detect-spice-boards.sh: opt-in boards (sim.yml), libs/spice and symbols,
    scripts/sim, sim/fixtures, workflow, Makefile, requirements, relevant tests
    - Run RC divider fixture when sim/fixtures/ or scripts-only (no sim.yml boards)
    - Matrix job: Docker KiCad export + ngspice + run_sim; upload report and netlists
    - Align KICAD_IMAGE pin with pr-checks.yml
    Slice 5 (GitHub Actions spice job) — issue #48
2026-04-30 feat(sim): slice 6 — docs, toolchain in reports, board README link (#55)
    * feat(sim): slice 6 — docs, toolchain in reports, board README link
    - Record kicad-cli version in sim/kicad_export_toolchain.txt during export
    - SPICE report: KiCad CLI, ngspice, and SIM_KICAD_DOCKER_IMAGE (CI)
    - Pass KICAD_IMAGE into board sim job as SIM_KICAD_DOCKER_IMAGE
    - Rewrite sim/README as implementation runbook; add BACKLOG-docker-image.md
    - tps63070-breakout README: artifact + example report link
2026-05-01 feat(sim): baseline metric deltas in reports (#58) (#64)
    * feat(sim): baseline metric deltas in Spice reports (#58)
    - Add committed optional sim/spice_metrics_baseline.json (schema v1)
    - Extend markdown report with Baseline and Δ columns; SIM_BASELINE_COMPARE footer
    - run_sim CLI: --baseline, --no-baseline, --write-baseline, --write-baseline-ref
    - Seed tps63070-breakout baseline; docs + pytest coverage
    Closes #58
2026-05-04 feat(board): expand esp32s3-devkit GPIO header to 17 pins (3.3 V)
    J2: Conn_01x16 → Conn_01x17 with matching PCB updates (decoupling, layout).
2026-05-04 ci: trigger README image workflow when fetch-3d-models.sh changes
2026-05-04 docs(sim): overlay contract and parasitic evolution path (#63) (#73)
    * docs(sim): overlay contract and parasitic evolution path (#63)
    Add OVERLAY-PARASITICS.md: assembler order, overlay vs libs/spice,
    schematic-only to extraction-backed fragments on same hook, non-goals.
    Link from sim/README.md; pointer in assemble.py docstring.
    * docs(sim): fix relative links in OVERLAY-PARASITICS.md
    Paths from sim/ need a single .. to reach repo root for boards/ and libs/spice/ links.
2026-05-04 docs: simulation roadmap — voltage reporting, impedance, EMI-adjacent goals
    Cross-link sim/README Future; board README § Simulation roadmap (long-term).
    Aligns with PR #78 discussion and PRD #43 scope notes.
2026-05-05 feat(sim): Stage-C extracted fragment hook for tps63070-breakout (#74) (#83)
    Add committed sim/extracted_hotloop_fragment.cir (comment stub) and .include
    it from overlay.cir before manual_parasitics.cir; mirror the same includes in
    ac_small_signal.cir so transient and secondary AC decks stay consistent.
    Document filenames, refresh contract, and reviewer expectations in
    OVERLAY-PARASITICS.md; cross-link from sim/README and board README.
2026-05-05 feat(sim): README SPICE summary, main-branch reports, richer metrics
    - Add spice-regression README fence + metrics-driven summary in update-board-readmes
    - Run ngspice on main when sim paths change; merge spice outputs into README commit
    - detect-spice-boards-for-push.sh scopes boards from push diff
    - Stop gitignoring boards/**/docs/spice-report.md and .metrics.json for bot commits
    - report_md: executive summary + results by scenario; sim.yml optional title/group
    - metrics JSON schema v2 with generated_at and display fields
2026-05-07 feat(spice): TPS63070 ngspice stub — FB-aware regulation + bootstrap
    Replace fixed 3.3 V output with an algebraic closure tied to V(FB) and V_REF,
    plus a short FB-abs bootstrap so OP/transient does not stick at Vout=0.
    Refresh tps63070-breakout baseline (~3.307 V nominal); update SHA256 + README.
2026-05-08 fix(sim): escape '|' in SPICE markdown tables (measure titles)
    Titles like |Zout| and AC |Vout| were parsed as extra columns in GFM
    pipe tables, leaving Measure empty in PR comments and excerpts.
    - report_md: escape_md_table_cell on measure rows and failure bullets
    - update-board-readmes: escape README regression table cells
    - compose-spice-report-comment.sh: jq esc helper for metrics rows
    - tests: unit test + integration assertions for escaped titles
2026-05-08 fix(ci): repo root on sys.path for update-board-readmes
    sim/report_md imports scripts.sim.baseline_metrics. The README updater only
    prepended scripts/, so GitHub Actions raised ModuleNotFoundError: scripts.
    Insert repo root after scripts/ so validate_board/sim resolve first, then
    scripts.* imports work.
2026-05-08 docs(tps63070): README order + 4L advanced fab DRC (#91)
    * docs(tps63070): README order + 4L advanced fab rules
    - Move simulation / SPICE regression below KiCad checks and validation.
    - Document fab intent: 2L advanced for ordering; CI also runs 4L-advanced decks.
    - Add jlcpcb-4layer-advanced & pcbway-4layer-advanced (.kicad_dru) and wire
    board.yml; extend root README fab table.
    * feat(esp32s3-devkit): target 4-layer advanced fab DRC rules
2026-05-08 ci(emi): openEMS + gerber2ems Docker + CI fixture (#92)
    * ci(emi): add openEMS + gerber2ems Docker fixture workflow
    - Self-contained emi/docker Dockerfile (pinned openEMS + gerber2ems SHAs).
    - run-emi-fixture.sh clones upstream stub_short at matching revision.
    - Path-filtered emi-checks workflow + workflow_dispatch; Makefile emi-fixture-docker.
    - Document scope vs chamber sign-off; link from root + sim README.
    * docs(emi): align wording with open-source EMS / openEMS
2026-05-24 fix(esp32s3-devkit): migrate J3 USB-C to 16P symbol and Connector_USB footprint.
    Use KiCad Connector USB‑C USB2 16P (A8/B8 SH) with the KiCad Connector_USB HRO footprint, remove the duplicated HRO footprint lib, refresh PCB pad SH naming, and add a small migration helper script.
2026-05-24 fix(esp32s3-devkit): align U1 GND stitch and hot loop with breakout layout
    Copy the tps63070-breakout triangle GND via pattern and L1/L2 routing so
    JLCPCB fab DRC clears hole-to-hole warnings without dropping stitch vias.
2026-05-27 ci: use KiBot v2_k10 for KiCad 10 board files (#98)
    Generate Fab Files was failing because boards are saved in KiCad 10 format while the workflow still used KiBot with KiCad 9.
2026-05-27 feat: commit generated fab files back to repo from CI
    Instead of only uploading artifacts (which expire), the workflow now
    commits gerbers, BOMs, and docs to boards/<board>/output/ so they're
    available locally after a pull. Also simplifies trigger to manual-only
    and removes the release-attachment step.
2026-05-31 ci: commit JLCPCB Gerber zip into board fab folder
    Copy the KiBot-generated JLCPCB ZIP into a stable committed path
    at boards/<board>/fab/jlcpcb/<board>-gerber.zip so that after the
    generated PR is merged, a local `git pull` provides a drag-and-drop
    file ready for JLCPCB upload.
    Narrows the create-pull-request step to only commit the Gerber ZIP
    instead of the entire output directory.
